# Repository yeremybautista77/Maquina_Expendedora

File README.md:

# Máquina Expendedora Vending ESP32

## 📌 Descripción del Proyecto

Nuestra **Máquina Expendedora** es un dispensador automático de productos de consumo (6 canales o espirales), diseñado con un enfoque de **industrial y bajo costo**. El sistema está controlado por un **microcontrolador ESP32** junto con una **pantalla táctil integrada de 4.0 pulgadas**, que actúa como cerebro y como interfaz gráfica. El firmware se desarrolla con **ESP-IDF** en **C nativo**.

El funcionamiento es el siguiente:

1. **Pago:** El diseño admite un **validador multimoneda** (Joyzan CH-926), que registra pulsos por valor (RD$ 1 = 1 pulso, RD$ 5 = 3 pulsos, RD$ 10 = 5 pulsos, RD$ 25 = 7 pulsos) a través de un **optoacoplador** de seguridad. El monedero está **habilitado** (`BOARD_COIN_ACCEPTOR_ENABLED = 1`) y el saldo también puede cargarse desde el panel de administración `ADM`.
2. **Selección:** El usuario navega por la pantalla táctil (diseñada en una cuadrícula de 2 columnas por 3 filas) para elegir el producto y la cantidad (máximo 10 unidades por canal).
3. **Despacho:** El ESP32 activa el relé correspondiente del motor reductor del canal seleccionado mediante el bus **I2C**. **M1–M4** usan un **sensor de posición** por un segundo PCF8574 (`0x21`): el motor gira hasta salir de `home`, avanza y se detiene al volver a `home`. **M5 y M6** operan en **lazo abierto por tiempo** (3 segundos). Si el `0x21` no responde, los 6 canales caen automáticamente a lazo abierto. Cada canal usa un **transistor NPN como inversor** entre el PCF8574 y el módulo de relé. Si se compra más de un producto, el firmware aplica un **Mutex** en FreeRTOS para que solo un motor rote a la vez (despacho secuencial). El pedido se encola de forma **atómica**: se acepta completo o se rechaza entero.

---

## 📊 Estado del Proyecto

**Firmware v1.0 (2026-11-05).** Compila sin errores ni warnings
(`maquina_expendedora.bin` = **588 560 B**, 44 % de la partición libre). Los **6
motores (M1–M6)**, la pantalla, el táctil y la NVS se validaron físicamente en
etapas anteriores.

**Fabricación:** gabinete armado y pintado, con el módulo de seis compartimentos,
los motores y las espirales instalados. Registro fotográfico en
`Documentacion/Proceso de manufactura/`. La PCB de interconexión está en diseño.

**Implementado:**
- GUI táctil 2×3 con modal de confirmación y panel inferior de saldo/total. Las
  imágenes de producto van **embebidas en flash** (52×52 RGB565); si falta una,
  se muestra `[Espacio Imagen]`.
- Despacho secuencial de 6 motores con Mutex. **M1–M4 con sensor de posición**
  (`0x21`); **M5–M6 por temporización** (3 s) y fallback a tiempo si el sensor no
  responde.
- Canal de potencia: PCF8574 `0x20` → transistor NPN inversor → módulo de relé de
  1 canal con jumper `H/L` en **LOW**.
- Encolado atómico todo-o-nada.
- Cobro diferido: el saldo y el stock solo se descuentan cuando se entrega la
  unidad. Las cantidades del carrito vuelven a cero al cerrar el pedido.
- Persistencia en NVS de saldo, stock y precios.
- Modo administración por botón `ADM` + contraseña (`20250456`): ajuste de
  saldo, inventario y precios.
- Monedero CH-926 habilitado por IO35 (1/3/5/7 pulsos).
- MicroSD desactivada (`BOARD_SD_ENABLED = 0`).

**Pendiente de validación física:**
- Montaje definitivo de los 6 motores: la prueba de banco se hizo con un solo
  motor recorriendo M1–M6 (relé y sensor respondieron en cada canal).
- Confirmar con multímetro que `home = LOW` y el divisor 10 kΩ/3.3 kΩ; el
  *homing* de arranque sigue desactivado por seguridad.
- Probar el monedero CH-926 con monedas reales.
- Definir nombre, precio e imagen de **P4–P6** (hoy provisionales RD$ 70/80/90).
- Pruebas automatizadas/CI y extras V2.0 (telemetría Wi-Fi, audio, RFID).

**Build de referencia:** `maquina_expendedora.bin` = **0x8fb10** (588 560 B),
**44 %** de la partición de aplicación libre.

---

## 🛠️ Materiales

### Control e Interfaz
- **1x Pantalla Táctil TFT (4.0 pulgadas):** Integra el ESP32-WROOM-32E, Wi-Fi/BT y puertos de expansión JST. Activa como la interfaz gráfica (GUI) del sistema.

### Sistema de Pago y Aislamiento
- **1x Monedero Multimoneda Joyzan (CH-926):** Lee monedas de RD$ 1, RD$ 5, RD$ 10 y RD$ 25 (operación a 12V).
- **1x Módulo Optoacoplador HiLetgo (PC817, 2 canales):** Aísla la señal de 12V del monedero y la transforma en una señal segura de 3.3V para el ESP32.

### Actuadores y Expansión I/O
- **4x Motores Reductores 12V DC (LK20052, 3 hilos):** Canales M1–M4, con sensor de posición.
- **2x Motores Reductores 12V DC (LK20052 Fy-007, 2 hilos):** Canales M5–M6, despachados por tiempo.
- **1x Módulo Expansor I2C PCF8574 (NOYITO - Rojo):** Configurado con sus DIP switches en la dirección `0x20` (relés). La PCB de interconexión usa solo **P0–P5** (6 canales); `P6`, `P7` e `INT` quedan sin conectar.
- **1x Módulo Expansor I2C PCF8574 adicional:** Dirección `0x21`, entradas para los sensores (alimentado a 3.3 V). La PCB cablea **P0–P5**: `P0`–`P3` para los sensores de M1–M4 y `P4`–`P5` **de reserva**, con su divisor ya montado, para cuando se cambien M5/M6 por motores con sensor.
- **1x PCB de interconexión (100 × 100 mm, 2 capas):** concentra el bus I2C, los dos expansores, las 6 etapas NPN, los 6 divisores y el acondicionamiento del monedero. No lleva 12 V ni contactos de potencia. Especificación: `Firmware/IDEA_PCB_CONEXIONES.md`.
- **4x Sensores de posición** (ópticos o micro-switch) con **divisor 10 kΩ en serie + 3.3 kΩ a GND** desde 12 V.
- **6x Módulos de Relé de 1 canal (SRD-12VDC-SL-C, bobina 12V, jumper `H/L` en LOW):** Uno por motor. La entrada `IN` se activa en LOW (0 V) y se desactiva en HIGH.
- **6x Transistores NPN + 6x Resistencias de 1 kΩ:** Inversor por canal entre el PCF8574 y la entrada `IN` del relé (`EMISOR`→GND, `BASE`→1 kΩ→P0…P5, `COLECTOR`→`IN`). El PCF8574 saca HIGH para encender.

### Potencia
- **1x Fuente Conmutada Principal:** 110V AC a 12V DC (mínimo 10 Amperios).
- **1x Módulo Step-Down DC-DC (LM2596):** Reduce los 12V a 5V exclusivamente para la entrada de la placa Hosyond.

---

## 🔌 Conexiones

### Alimentación
- **Línea 12V:** Alimenta el monedero, las bobinas de los 6 relés, las terminales de carga (COM/NO) y la entrada del Step-Down.
- **Línea 5V (desde el Step-Down):** Exclusiva de la entrada de 5V de la placa Hosyond. No alimenta relés ni motores.
- **Línea 3.3V:** Generada por el regulador de la placa Hosyond para el ESP32, el PCF8574 y los periféricos lógicos.
- **Tierras:** el GND lógico del ESP32, el GND del Step-Down y el GND del módulo de relés se atornillan juntos al borne **V− / COM** de la fuente de 12V (punto estrella).

### Monedero (vía Optoacoplador PC817)
- **Lado 12V (entrada):** `IN1` recibe la señal (pulso) del monedero y cierra el circuito al `GND` de la fuente de 12V.
- **Lado 3.3V (salida al ESP32):** `VCC` (3.3V) y `GND` provienen de la pantalla; el pin de señal `OUT1` se conecta al pin digital **IO35** del puerto *Expand the input pin*.

### Bus I2C y Expansor (PCF8574)
- El módulo expansor se conecta al puerto *I2C Peripheral Interface* de la pantalla (SDA, SCL, 3.3V, GND).
- **Expansor de relés (dirección 0x20):** los pines P0–P5 van a la **base** de cada transistor NPN a través de 1 kΩ; el colector va al `IN` de cada módulo de relé y el emisor a GND.
- **Expansor de sensores (dirección 0x21):** P0–P3 reciben la señal de los sensores de posición **M1–M4** a través de los divisores 10 kΩ / 3.3 kΩ. **P4 y P5 llevan el mismo divisor montado pero sin sensor: quedan de reserva** para futuros motores con sensor. El módulo se alimenta a 3.3 V. `home = LOW` (`BOARD_SENSOR_HOME_LEVEL = 0`), pendiente de confirmar con multímetro.

*Nota de polaridad:* el módulo de relé queda con el **jumper `H/L` en LOW** (su entrada `IN` se activa con 0 V). Como el transistor NPN **invierte** la señal, el PCF8574 debe sacar **HIGH (3.3 V)** para encender el motor y **LOW (0 V)** para apagarlo. Por eso `BOARD_RELAY_ACTIVE_LOW = 0` y el registro sombra se escribe sin invertir. En el log se ve `0x20 = 0x01` al encender M1 y `0x20 = 0x00` al apagar.

---

## 🔐 Modo Administración (operador)

El panel está protegido con contraseña y se usa para mantenimiento de la máquina.

1. **Acceso:** pulsa el botón pequeño **`ADM`** que está junto a `Confirmar`, en el panel inferior.
2. Introduce la contraseña **`20250456`** (8 dígitos) en el teclado numérico. Al teclear el octavo dígito se valida sola; `C` borra y `OK` reintenta el envío.
3. Se abre un panel con scroll y tres secciones:
   - **Saldo:** muestra el saldo actual y permite subirlo o bajarlo con `+1/+5/+10/+25` y `-1/-5/-10/-25`. Cada cambio se guarda en NVS al instante.
   - **Inventario:** muestra el stock de los 6 canales y el botón `Rellenar Stock (Reset a 10)`.
   - **Precios:** cada producto tiene `[-]`/`[+]` en pasos de **RD$ 5**. Pulsa `Guardar Precios` para aplicar los cambios y persistirlos en NVS. Rango válido: RD$ 5.00–1000.00.
4. Cierra el panel con el botón **X**.

**Seguridad:** el acceso, el ajuste de saldo, el reset y el guardado de precios se bloquean mientras hay una compra activa. La contraseña es provisional y se valida en el firmware.

---

## ✍️ Autores

- Sebastian Josue Diaz Encarnación (2025-0533)
- Lia Camille Figuereo Sanchez (2025-0443)
- Wilmalis Perez Vargas (2025-0461)
- Lia Marie Hernandez Corsino (2025-0452)
- Yeremy Manuel Bautista Portes (2025-0456)

---

## 📁 Estructura del Repositorio

```
Maquina_Expendedora/
├── Firmware/                         C + ESP-IDF + FreeRTOS
├── Diseño_electronico/
│   ├── ARQUITECTURA_HARDWARE.md      dominios de voltaje, cableado y pines
│   ├── img/                          figuras del documento
│   └── PCB/                          KiCad: esquema, PCB y PDFs de fabricación
├── Diseño_mecanico/
│   ├── Chasis/                       piezas y ensamblaje del gabinete
│   └── motor dc/                     motor, espiral y base
├── cad/                              referencia 2D del módulo PCF8574
├── Documentacion/
│   ├── Documentacion Tecnica/        arquitectura del sistema
│   └── Proceso de manufactura/       registro fotográfico del armado
├── Documentacion Proyecto Terminado/ entrega final (en preparación)
└── backups_firmware/                 respaldo local de la flash (no versionado)
```

## 📚 Documentación

| Documento | Para qué sirve |
| :--- | :--- |
| `Firmware/README.md` | Compilar, flashear y operar el firmware |
| `Firmware/ESTADO_DEL_PROYECTO.md` | Bitácora técnica: qué está hecho, qué falta y riesgos conocidos |
| `Firmware/IDEA_PCB_CONEXIONES.md` | Mapa de pines, BOM y reglas de la PCB de interconexión |
| `Diseño_electronico/ARQUITECTURA_HARDWARE.md` | Voltajes, cableado, protecciones y pines del ESP32 |
| `Diseño_electronico/PCB/` | Esquema y PCB en KiCad, con PDFs de fabricación |
| `Diseño_mecanico/README.md` | Inventario de piezas y ensamblajes del chasis |
| `Documentacion/Documentacion Tecnica/` | Arquitectura del sistema y flujo de una compra |
| `Documentacion/Proceso de manufactura/` | Fotos del armado del gabinete y del módulo de despacho |

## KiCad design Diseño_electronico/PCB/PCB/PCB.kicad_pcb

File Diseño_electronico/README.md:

# Diseño electrónico

Documentación eléctrica del sistema y proyecto de la **PCB de interconexión**.

## Contenido

| Ruta | Contenido |
| :--- | :--- |
| `ARQUITECTURA_HARDWARE.md` | Dominios de voltaje (12 V / 5 V / 3.3 V), topología, protecciones, calibres de conductor, mapa de pines del ESP32 y criterios de armado |
| `img/` | Figuras referenciadas por el documento de arquitectura |
| `PCB/` | Proyecto KiCad de la placa de conectores y PDFs de fabricación |

## PCB de interconexión

Placa de 100 × 100 mm, 2 capas, que concentra el bus I2C, los dos expansores
PCF8574, las seis etapas NPN de relé, los divisores de los sensores y el
acondicionamiento del monedero. **No lleva 12 V ni contactos de potencia**: eso queda
en la bornera de los módulos de relé.

| Archivo | Uso |
| :--- | :--- |
| `PCB/PCB/PCB.kicad_sch` | Esquema eléctrico |
| `PCB/PCB/PCB.kicad_pcb` | Editor de PCB |
| `PCB/PCB/PCB.kicad_pro` | Proyecto KiCad |
| `PCB/Pistas.pdf` | Impresión de la capa de pistas |
| `PCB/Silkscreen.pdf` | Serigrafía para revisión antes de fabricar |

> `PCB/PCB.zip` es el respaldo del proyecto completo y se conserva **fuera de Git**
> (2.2 MB). Los archivos `.kicad_sch`, `.kicad_pcb` y `.kicad_pro` sí están
> versionados y bastan para reabrir el proyecto.

**Estado:** huellas colocadas; falta sincronizar los nets desde el esquema y rutear.
El mapa de pines, el BOM y las reglas de diseño están en
`../Firmware/IDEA_PCB_CONEXIONES.md`.

> La placa se rotula con `M0`–`M5` y el firmware numera los canales `M1`–`M6`: es el
> mismo canal desplazado en uno. Está anotado en `../Firmware/IDEA_PCB_CONEXIONES.md` §8.

## Pendiente

- [ ] Sincronizar el PCB desde el esquema y rutear.
- [ ] Verificar ERC/DRC sin errores antes de mandar a fabricar.
- [ ] Unificar el pin del monedero: la placa dice `IO39` y el firmware lee `GPIO35`.

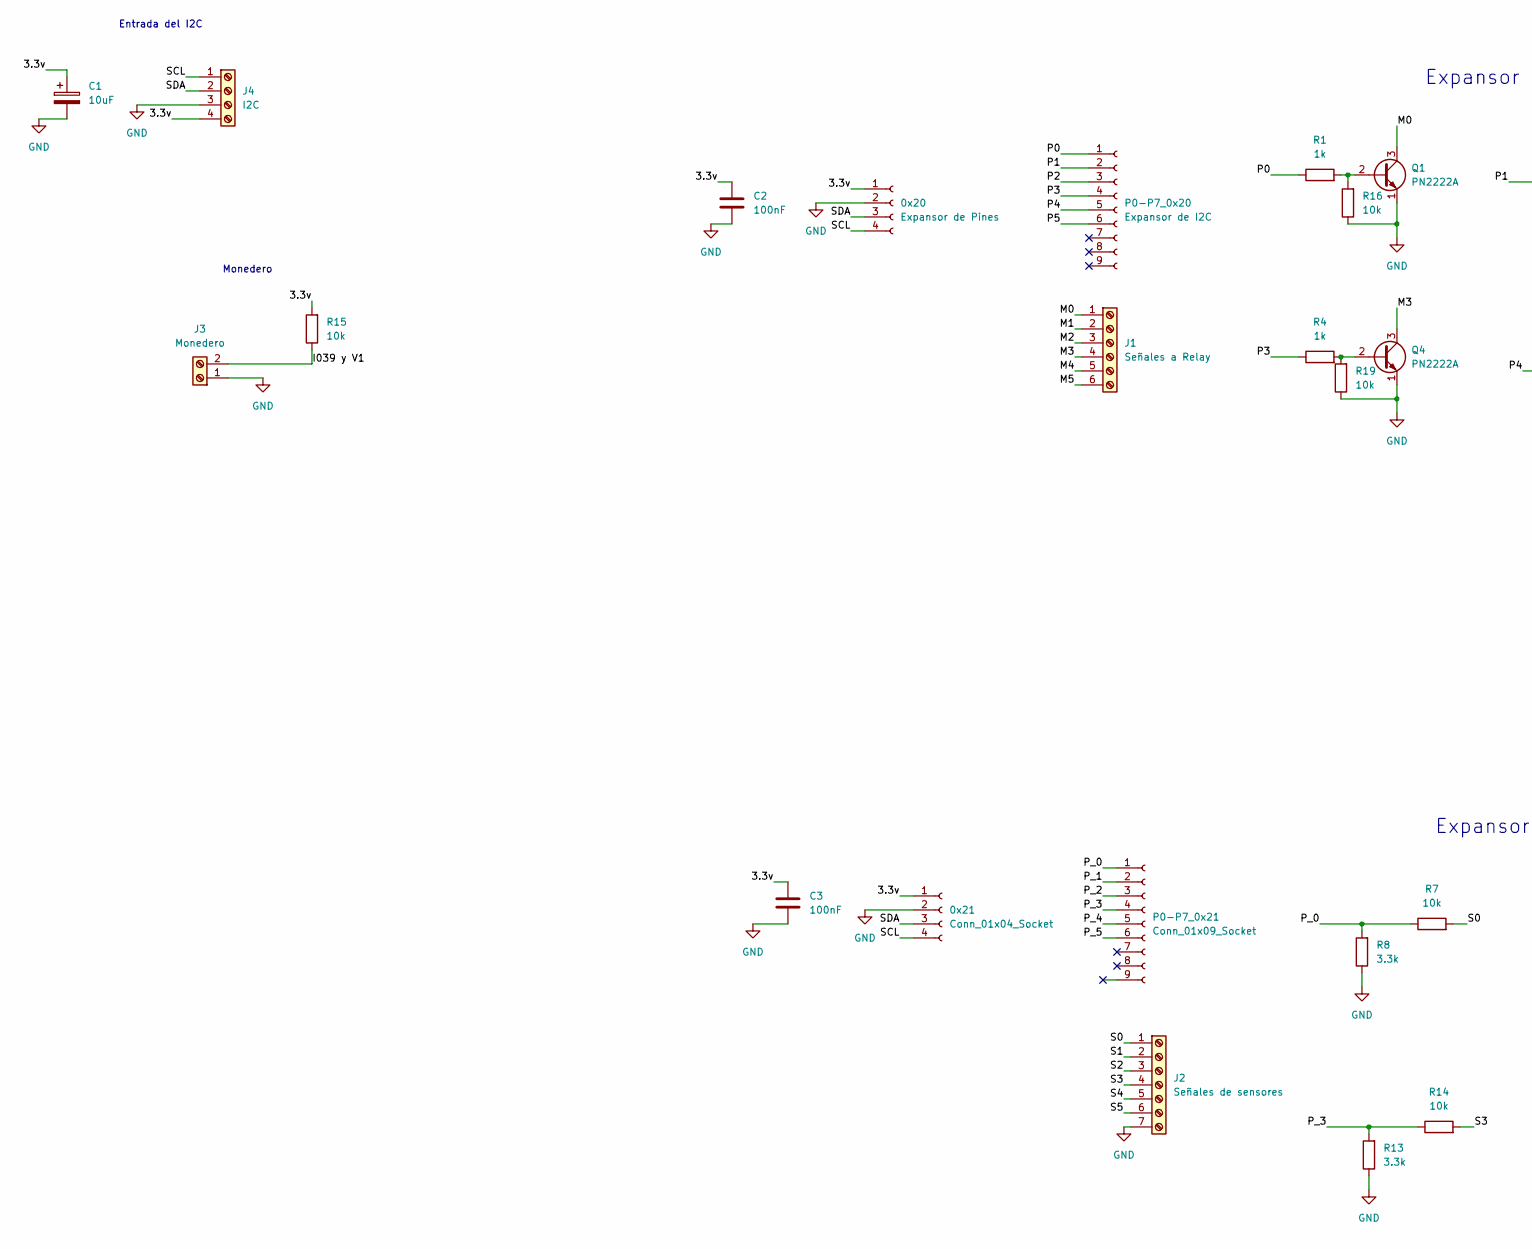
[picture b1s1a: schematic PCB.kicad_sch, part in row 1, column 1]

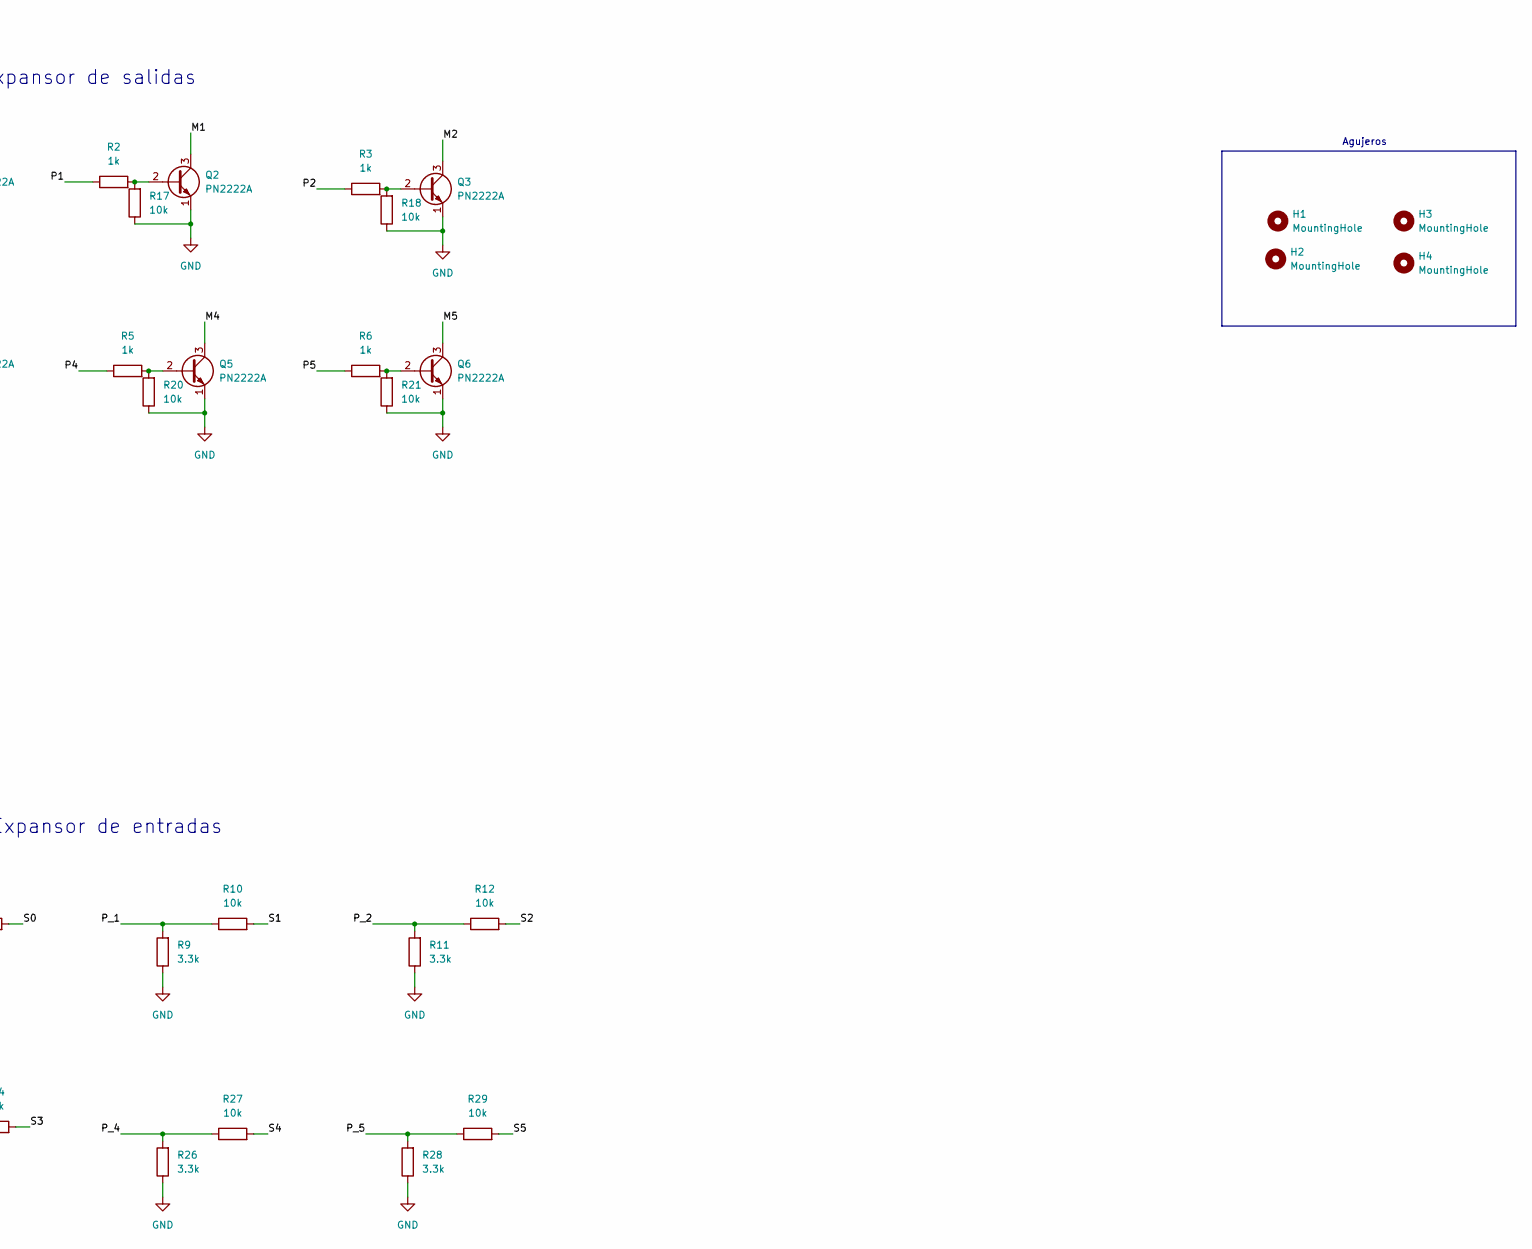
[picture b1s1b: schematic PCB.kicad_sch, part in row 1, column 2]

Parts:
0x20: Expansor de Pines; PinSocket_1x04_P2.54mm_Vertical
0x21: Conn_01x04_Socket; PinSocket_1x04_P2.54mm_Vertical
C1: 10uF; CP_Radial_D5.0mm_P2.00mm
C2, C3: 100nF; C_Disc_D5.0mm_W2.5mm_P5.00mm
H1, H2, H3, H4: MountingHole; MountingHole_4.3mm_M4
J1: Señales a Relay; TerminalBlock_Phoenix_MKDS-1,5-6-5.08_1x06_P5.08mm_Horizont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
J2: Señales de sensores; TerminalBlock_Phoenix_MKDS-1,5-7-5.08_1x07_P5.08mm_Horizont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
J3: Monedero; TerminalBlock_Phoenix_MKDS-1,5-2-5.08_1x02_P5.08mm_Horizont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
J4: I2C; TerminalBlock_Phoenix_MKDS-1,5-4-5.08_1x04_P5.08mm_Horizont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
P0-P7_0x20: Expansor de I2C; PinSocket_1x09_P2.54mm_Vertical
P0-P7_0x21: Conn_01x09_Socket; PinSocket_1x09_P2.54mm_Vertical
Q1, Q2, Q3, Q4, Q5, Q6: PN2222A; TO-92_Inline
R1, R2, R3, R4, R5, R6: 1k; R_Axial_DIN0207_L6.3mm_D2.5mm_P10.16mm_Horizontal
R7, R10, R12, R14, R15, R16, R17, R18, R19, R20, R21, R27, R29: 10k; R_Axial_DIN0207_L6.3mm_D2.5mm_P10.16mm_Horizontal
R8, R9, R11, R13, R26, R28: 3.3k; R_Axial_DIN0207_L6.3mm_D2.5mm_P10.16mm_Horizontal

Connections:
/3.3v: 0x20.1, 0x21.1, C1.1, C2.1, C3.1, J4.4, R15.2
/I039 y V1: J3.2, R15.1
/M0: J1.1, Q1.3 (C)
/M1: J1.2, Q2.3 (C)
/M2: J1.3, Q3.3 (C)
/M3: J1.4, Q4.3 (C)
/M4: J1.5, Q5.3 (C)
/M5: J1.6, Q6.3 (C)
/P0: P0-P7_0x20.1, R1.1
/P1: P0-P7_0x20.2, R2.1
/P2: P0-P7_0x20.3, R3.1
/P3: P0-P7_0x20.4, R4.1
/P4: P0-P7_0x20.5, R5.1
/P5: P0-P7_0x20.6, R6.1
/P_0: P0-P7_0x21.1, R7.1, R8.2
/P_1: P0-P7_0x21.2, R9.2, R10.1
/P_2: P0-P7_0x21.3, R11.2, R12.1
/P_3: P0-P7_0x21.4, R13.2, R14.1
/P_4: P0-P7_0x21.5, R26.2, R27.1
/P_5: P0-P7_0x21.6, R28.2, R29.1
/S0: J2.1, R7.2
/S1: J2.2, R10.2
/S2: J2.3, R12.2
/S3: J2.4, R14.2
/S4: J2.5, R27.2
/S5: J2.6, R29.2
/SCL: 0x20.4, 0x21.4, J4.1
/SDA: 0x20.3, 0x21.3, J4.2
GND: 0x20.2, 0x21.2, C1.2, C2.2, C3.2, J2.7, J3.1, J4.3, Q1.1 (E), Q2.1 (E), Q3.1 (E), Q4.1 (E), Q5.1 (E), Q6.1 (E), R8.1, R9.1, R11.1, R13.1, R16.1, R17.1, R18.1, R19.1, R20.1, R21.1, R26.1, R28.1
unnamed: Q1.2 (B), R1.2, R16.2
unnamed: Q2.2 (B), R2.2, R17.2
unnamed: Q3.2 (B), R3.2, R18.2
unnamed: Q4.2 (B), R4.2, R19.2
unnamed: Q5.2 (B), R5.2, R20.2
unnamed: Q6.2 (B), R6.2, R21.2

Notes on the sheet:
Monedero
Agujeros
Expansor de salidas
Entrada del I2C
Expansor de entradas

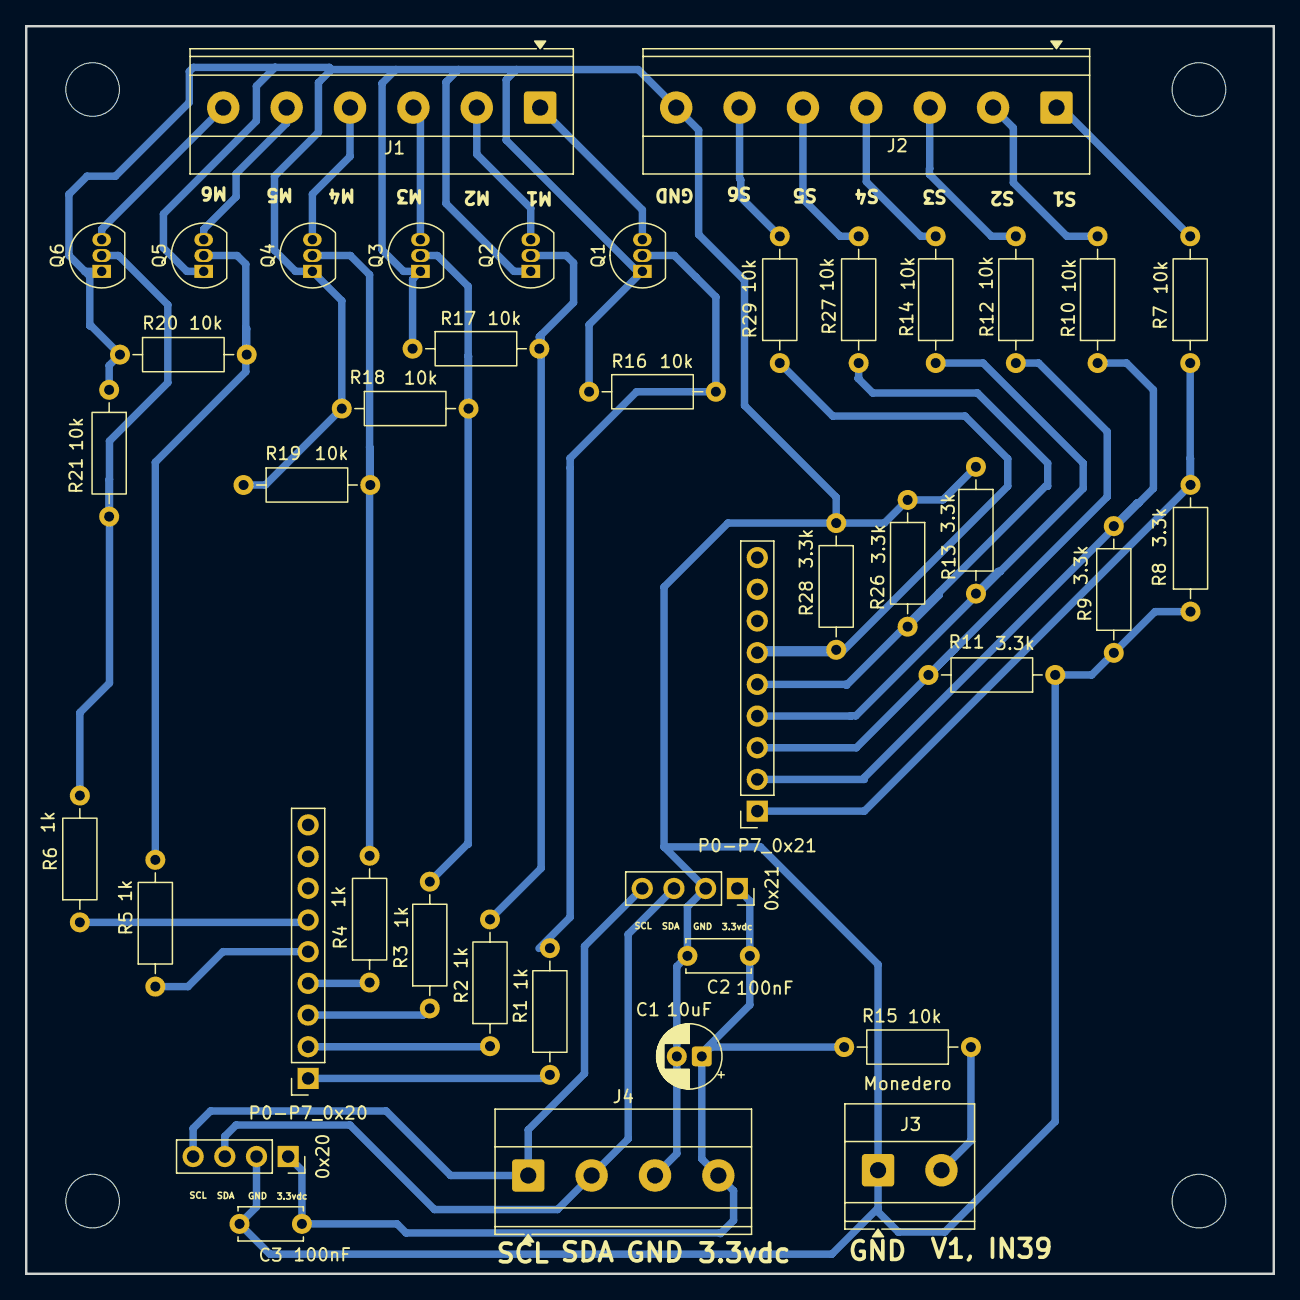
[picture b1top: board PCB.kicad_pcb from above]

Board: 2 copper layers, 100.0 x 100.0 mm, 46 parts (0 on the bottom side), 35 nets.
